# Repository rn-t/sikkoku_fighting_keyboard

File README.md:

# sikkoku_fighting_keyboard
格闘ゲーム向けのキーボード型コントローラー

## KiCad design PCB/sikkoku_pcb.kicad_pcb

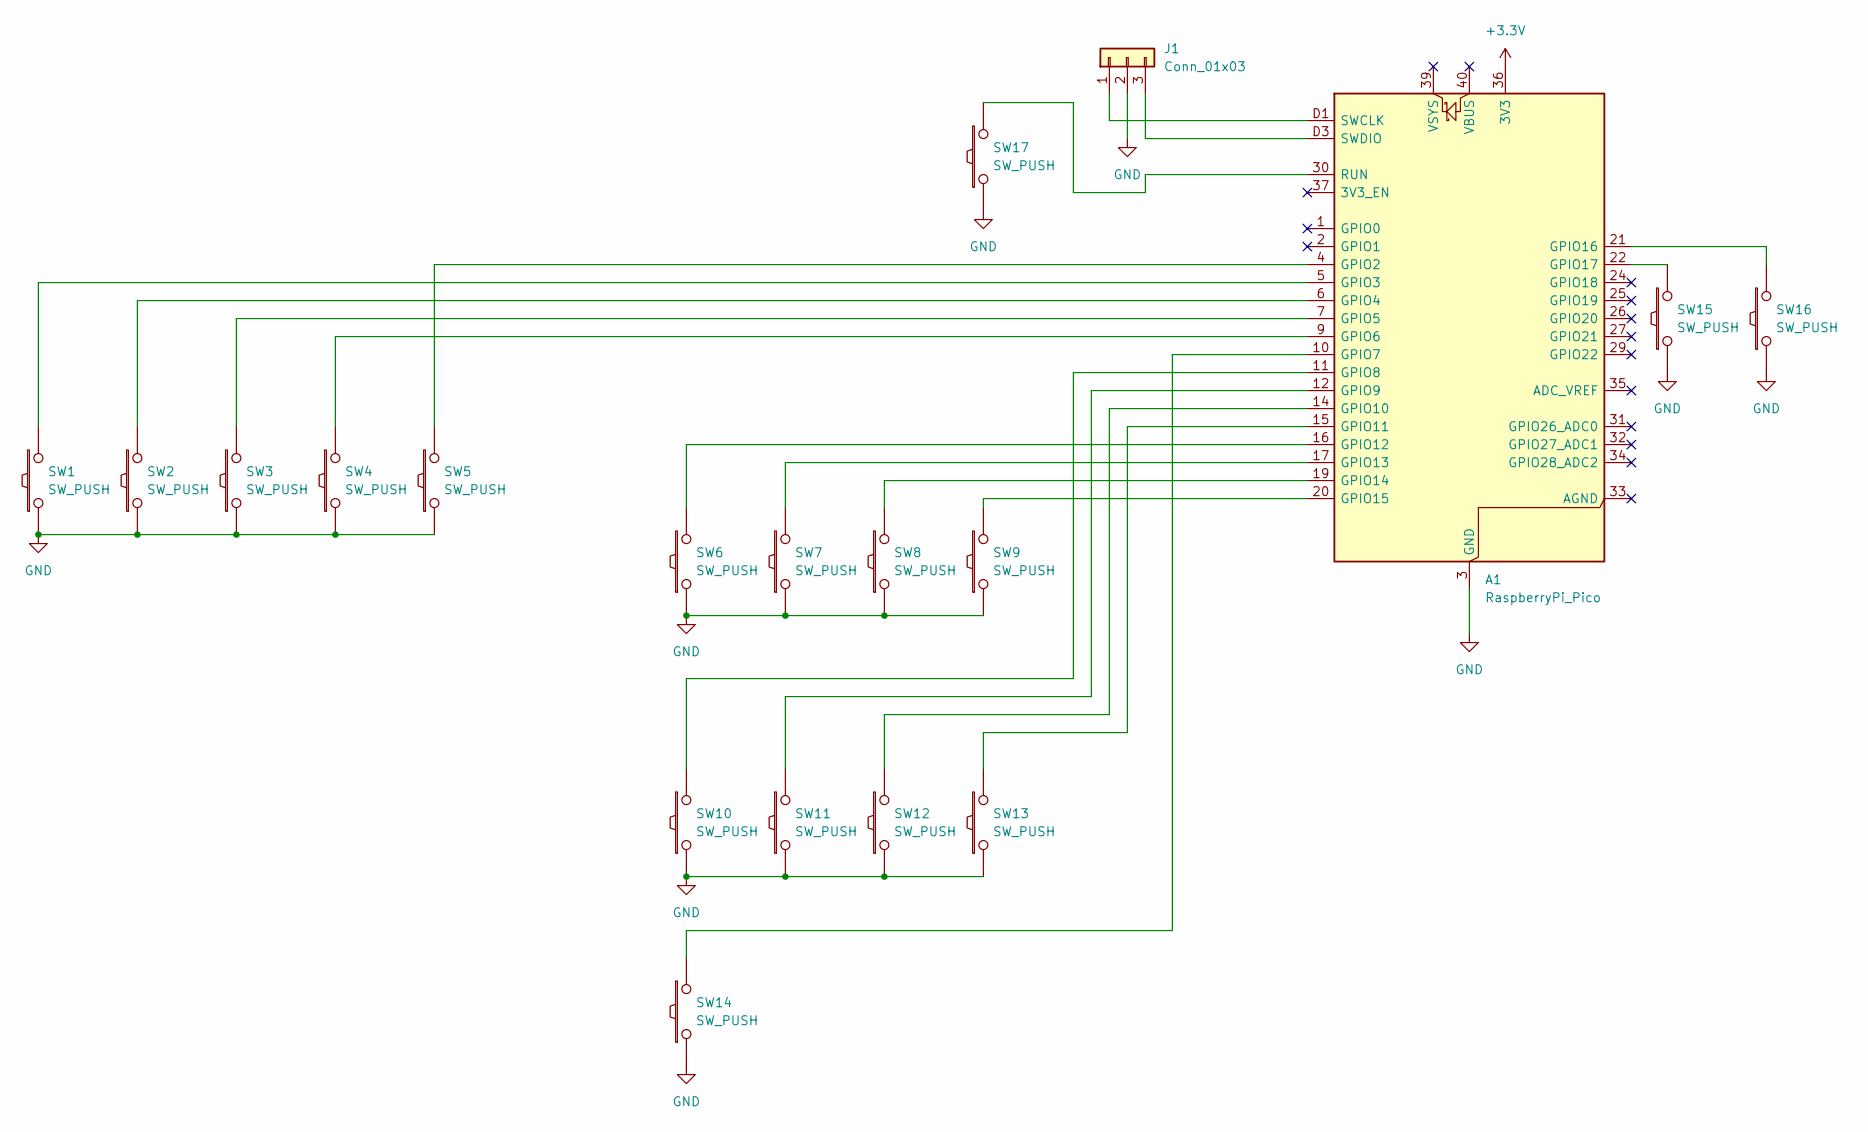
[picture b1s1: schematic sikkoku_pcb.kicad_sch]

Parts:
A1: RaspberryPi_Pico; RaspberryPi_Pico_SMD_HandSolder
J1: Conn_01x03; PinHeader_1x03_P2.54mm_Vertical
SW1, SW2, SW3, SW4, SW5, SW6, SW7, SW8, SW9, SW10, SW11, SW12, SW13, SW14, SW15, SW16: SW_PUSH; Kailh_Choc_V1_Hotswap_via
SW17: SW_PUSH; SW_SPST_PTS810

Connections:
+3.3V: A1.36 (3V3)
GND: A1.3 (GND), A1.8 (GND), A1.13 (GND), A1.18 (GND), A1.23 (GND), A1.28 (GND), A1.38 (GND), A1.D2 (GND), J1.2, SW1.1, SW2.1, SW3.1, SW4.1, SW5.1, SW6.1, SW7.1, SW8.1, SW9.1, SW10.1, SW11.1, SW12.1, SW13.1, SW14.1, SW15.1, SW16.1, SW17.1
unnamed: A1.4 (GPIO2), SW5.2
unnamed: A1.5 (GPIO3), SW1.2
unnamed: A1.6 (GPIO4), SW2.2
unnamed: A1.7 (GPIO5), SW3.2
unnamed: A1.9 (GPIO6), SW4.2
unnamed: A1.10 (GPIO7), SW14.2
unnamed: A1.11 (GPIO8), SW10.2
unnamed: A1.12 (GPIO9), SW11.2
unnamed: A1.14 (GPIO10), SW12.2
unnamed: A1.15 (GPIO11), SW13.2
unnamed: A1.16 (GPIO12), SW6.2
unnamed: A1.17 (GPIO13), SW7.2
unnamed: A1.19 (GPIO14), SW8.2
unnamed: A1.20 (GPIO15), SW9.2
unnamed: A1.21 (GPIO16), SW16.2
unnamed: A1.22 (GPIO17), SW15.2
unnamed: A1.30 (RUN), SW17.2
unnamed: A1.D1 (SWCLK), J1.1
unnamed: A1.D3 (SWDIO), J1.3

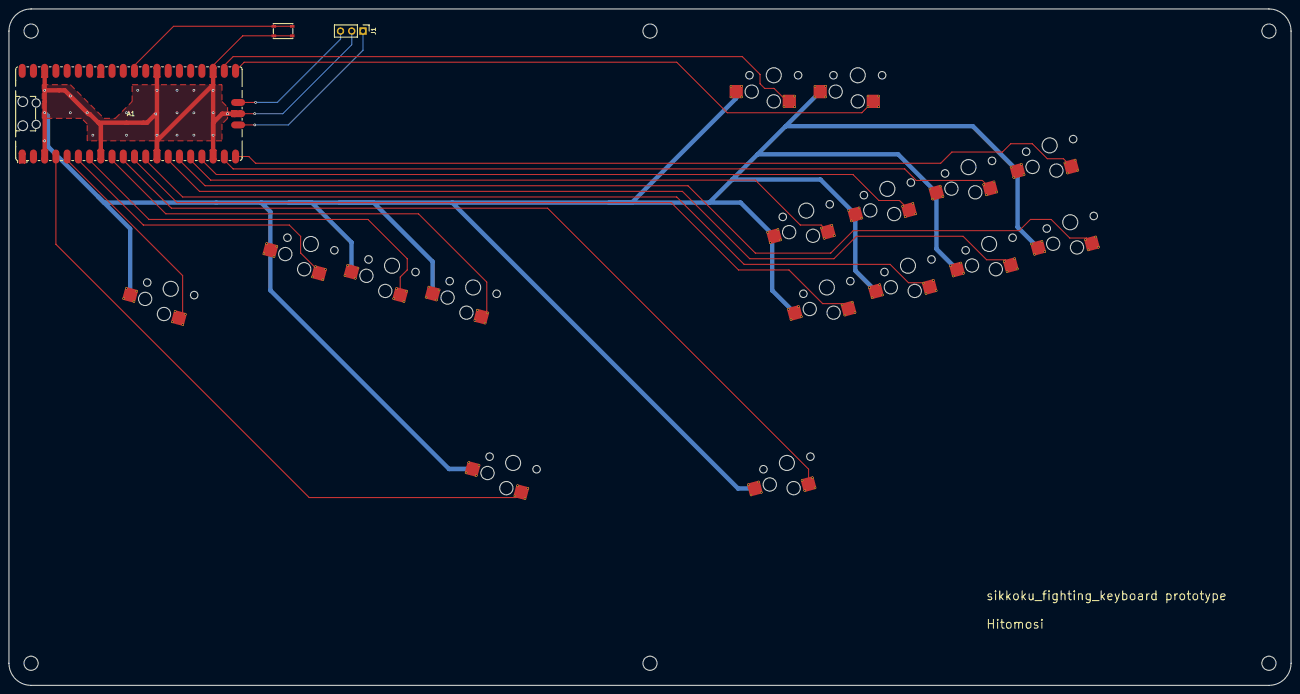
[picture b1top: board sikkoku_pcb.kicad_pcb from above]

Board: 2 copper layers, 290.0 x 153.0 mm, 19 parts (0 on the bottom side), 20 nets.

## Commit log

2025-05-08 KiCadプロジェクトファイルとgitignoreを追加
2025-05-08 BrownSugar_KBD_KiCad_Libraryを追加 追加に伴いライセンスを更新
2025-05-09 回路図が完成 ERC済
2025-05-10 部品配置が完了
2025-05-11 配線が完了 DRC済
2025-05-11 名前とかのシルクを追加
2025-05-11 gerber_to_orderを用いてガーバーデータ作成 発注
